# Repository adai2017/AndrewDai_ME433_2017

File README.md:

Andrew Dai
3/28/2017

GitHub Repository for MECH_ENG 433
Northwestern University - Spring 2017

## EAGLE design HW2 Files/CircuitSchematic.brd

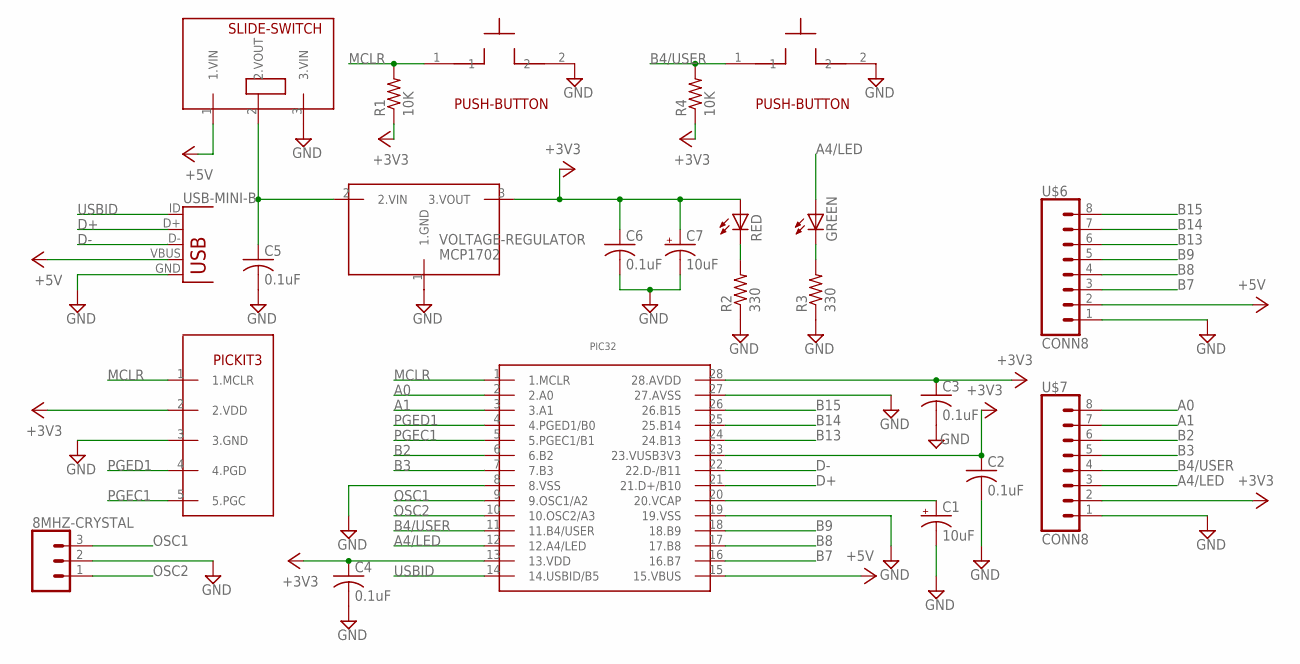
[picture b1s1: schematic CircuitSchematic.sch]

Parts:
8MHZ-CRYSTAL: CONN_03; 1X03
C1, C7: 10uF; E5-5
C2, C3, C4, C5, C6: 0.1uF; C025-025X050
GREEN: LED3MM
R1, R4: 10K; 0207/10
R2, R3: 330; 0207/10
RED: LED3MM
U$1: SLIDE-SWITCH; SLIDE-SWITCH-2
U$2, U$3: PUSH-BUTTON
U$4: PIC32; DIP28
U$5: PICKIT3
U$6, U$7: CONN8
USB-MINI-B: USB-MB-H
VOLTAGE-REGULATOR: MCP1702; TO92

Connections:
+3V3: C2.1, C3.1, C4.1, C6.1, C7.+, R1.1, R4.1, RED.A, U$4.13 (13.VDD), U$4.23 (23.VUSB3V3), U$4.28 (28.AVDD), U$5.2 (2.VDD), U$7.2, VOLTAGE-REGULATOR.3 (3.VOUT)
+5V: U$1.1 (1.VIN), U$4.15 (15.VBUS), U$6.2, USB-MINI-B.VBUS
A0: U$4.2 (2.A0), U$7.8
A1: U$4.3 (3.A1), U$7.7
A4/LED: GREEN.A, U$4.12 (12.A4/LED), U$7.3
B2: U$4.6 (6.B2), U$7.6
B3: U$4.7 (7.B3), U$7.5
B4/USER: R4.2, U$3.1, U$4.11 (11.B4/USER), U$7.4
B7: U$4.16 (16.B7), U$6.3
B8: U$4.17 (17.B8), U$6.4
B9: U$4.18 (18.B9), U$6.5
B13: U$4.24 (24.B13), U$6.6
B14: U$4.25 (25.B14), U$6.7
B15: U$4.26 (26.B15), U$6.8
D+: U$4.21 (21.D+/B10), USB-MINI-B.D+
D-: U$4.22 (22.D-/B11), USB-MINI-B.D-
GND: 8MHZ-CRYSTAL.2, C1.-, C2.2, C3.2, C4.2, C5.2, C6.2, C7.-, R2.1, R3.1, U$1.3 (3.VIN), U$2.2, U$3.2, U$4.8 (8.VSS), U$4.19 (19.VSS), U$4.27 (27.AVSS), U$5.3 (3.GND), U$6.1, U$7.1, USB-MINI-B.GND, VOLTAGE-REGULATOR.1 (1.GND)
MCLR: R1.2, U$2.1, U$4.1 (1.MCLR), U$5.1 (1.MCLR)
unnamed: C1.+, U$4.20 (20.VCAP)
unnamed: R2.2, RED.K (C)
unnamed: GREEN.K (C), R3.2
unnamed: C5.1, U$1.2 (2.VOUT), VOLTAGE-REGULATOR.2 (2.VIN)
OSC1: 8MHZ-CRYSTAL.3, U$4.9 (9.OSC1/A2)
OSC2: 8MHZ-CRYSTAL.1, U$4.10 (10.OSC2/A3)
PGEC1: U$4.5 (5.PGEC1/B1), U$5.5 (5.PGC)
PGED1: U$4.4 (4.PGED1/B0), U$5.4 (4.PGD)
USBID: U$4.14 (14.USBID/B5), USB-MINI-B.ID

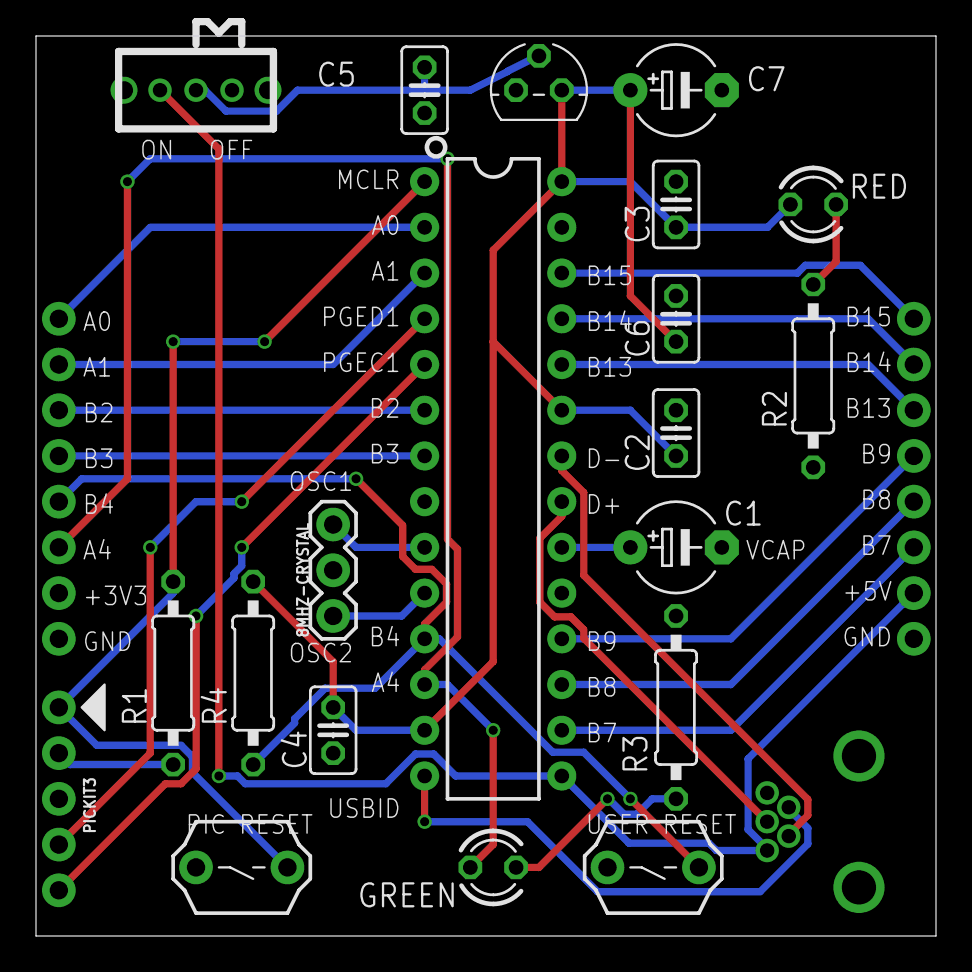
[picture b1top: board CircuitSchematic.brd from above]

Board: 2 copper layers, 50.0 x 50.0 mm, 23 parts (0 on the bottom side), 27 nets.

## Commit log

2017-03-28 :circus_tent: Added .gitattributes & .gitignore files
2017-03-28 Initial commit
    Readme file for GitHub
2017-03-29 Added regulator pictures
2017-03-30 Initial commit
    Added code files
    Updated HW1 pictures
2017-03-30 Dimmed LED
2017-03-30 Final HW 1 files
2017-03-30 Fixed errors
    Completed HW1 files
2017-03-30 Updated main.c
2017-04-03 WIP schematic
2017-04-04 Completed schematic
2017-04-04 GitHub commit for HW2
    - WIP board
    - Completed schematic
    - Completed library file
2017-04-06 Completed PCB
    To Do:
    - Add silkscreen pin names
    - Error checking
2017-04-06 Complete PCB with labels
    To do:
    - Add pictures
    - Add name and info
2017-04-06 Added missing connections
    To do:
    - Add pictures
    - Add name and info
2017-04-07 HW3 commit
    - Updated folder "HW2 Files"
    - Removed unnecessary project files
    - Added final schematic/pcb
    - Added .zip of gerber files
2017-04-07 Updated HW3 commit
    - Moved .brd and .sch files into folder "HW3 Files"
2017-04-13 HW4 commit
2017-04-13 Fixed period for HW4 main.c
2017-04-17 Updated HW4 and HW5 code
2017-04-17 Initial HW4 commit
2017-04-18 Final HW4 and HW5 commits - Initial HW6 commit
2017-04-18 Initial HW6 commit
2017-04-18 Added circuit diagrams
2017-04-18 HW6 WIP
2017-04-19 Final HW6 commit
2017-04-19 Added HW6 circuit diagram
2017-04-19 Initial HW7 commit
2017-04-19 HW7 commit
2017-04-20 Updated HW7 circuit diagram
2017-04-21 HW7 and initial HW8 commit
2017-04-21 HW7 WIP
2017-04-25 HW7 WIP - X bar working
2017-04-25 HW7 final commit
2017-04-25 Changed color for better video
2017-04-25 Restored previously correct circuit diagram
2017-04-25 Removed unnecessary files
2017-04-25 Initial HW8 commit
2017-04-25 Updated HW8 commit
2017-04-25 HW8 WIP
2017-04-25 Final HW8 commit
2017-05-03 HW11 initial commit
2017-05-15 HW WIP
2017-05-15 HW10 initial commit
2017-06-02 HW12 initial commit
    Hello world
2017-06-02 Completed HW12 commit
    Added bar
2017-06-02 Moved HW12 folder
    HelloWorld folder constantly updated, individual HW assignments will be
    copied into respective folders after completion
2017-06-02 HW13 commit
2017-06-02 HW13 WIP
2017-06-05 HW13 WIP
    Camera finds green but is still laggy
2017-06-05 Final HW13 code
    Laggy is okay -- will debug later if necessary
2017-06-05 Restart HW9
    Deleted old HW9 folder
2017-06-05 New HW9 initial commit
    Restarted HW9 before HW14
2017-06-05 Completed HW9 commit
    Checks 100Hz for 'r', outputs 100 IMU values
2017-06-05 Initial HW14 commit
    Copied CDC code from HW9
2017-06-05 HW14 WIP
2017-06-05 HW14 WIP
    Added Android app
2017-06-05 Final HW14 commit
    Functional
2017-06-06 Updated bug in HW13
2017-06-06 Initial HW20 commit
    Added additional HW folders for future commits
2017-06-06 HW18 initial commit
    Started HW18 motor control testing app
2017-06-07 Random commit
2017-06-08 HW18 final commit
    Putty / Android able to communicate with motors
2017-06-08 HW19 initial commit
    Begin ImageProcessing
2017-06-08 HW20 commit
    Restarted Android merging
    New PIC code
    Some HW19 changes
2017-06-08 New HW20 Android code
    Begin USB and Camera merge in Android code
2017-06-08 HW20 commit
    Merged Android and USB
2017-06-08 Updated HW20 commit
    Moved PWM error adjustments from PIC to Android
2017-06-08 HW20 tuning
2017-06-10 Final HW20 tuning
    Completed class
2017-06-11 Final HW15 commit
    Uploaded design files
2017-06-11 HW16 final commit
    Uploaded pictures
2017-06-11 HW17 final commit
    Uploaded pictures

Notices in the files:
parts and their libraries:
SparkFun-Connectors: Licensing: Creative Commons ShareAlike 4.0 International - https://creativecommons.org/licenses/by-sa/4.0
